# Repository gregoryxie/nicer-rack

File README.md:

# nicer-rack

hopefully nicer and not worser

View [NiceRack](http://nicerack.mit.edu:3000/)

## Installation

After downloading the repo, install all necessary depencies by running in the root folder:
`pip3 install -r requirements.txt`

## Accessing Raspberry Pi

On your own machine, SSH into the Raspi: `ssh putz@18.18.248.96`

Ask for the password if you need it. From here, you can access the Raspberry Pi's Software Configuration Tool (settings): `sudo raspi-config`

**Don't mess around with the settings.** But, if you want to update the Raspi, navigate to `8 Update` using the arrow keys, and hit enter to update. When it's done, tab your way to `Finish`, then hit enter.

You can navigate the filesystem the way any computer works. Some potentially useful commands:
* `sudo reboot`
* `sudo shutdown -h now` will safely shut down the Raspi
* `wget [url]` will download the file at the given URL to the Raspi, in whatever your working directory is.

## Web server

After making changes to config files, run `apache2ctl configtest` and make sure it doesn't throw any errors.

The main page of this site is located (on default) at `/var/www/html/index.html`. You can look at the config documentation at `/usr/share/doc/apache2/README.Debian.gz`. By default, Debian does not allow access through the web browser to any file apart of those located in `/var/www`, **public_html** directories (when enabled) and `/usr/share` (for web applications). If your site is using a web document root located elsewhere (such as in `/srv`) you may need to whitelist your document root directory in `/etc/apache2/apache2.conf`.

If you're having connection timeout issues or otherwise want to change server settings, go look at the `etc/apache2/apache2.conf` file.

To change folder location of `index.html` file:
* Change the DocumentRoot field in the config file to the correct filepath
* The default config file is at `/etc/apache2/sites-available/000-default.conf`, but you can find the nicerack config file at `etc/apache2/sites-available/nicerack.conf`
* Current location: /var/www/nicer-rack/nicer_rack_web/client/dist
* Restart apache server using `service apache2 restart`

For issues with installing llvmlite, try the following where # is the llvm version (integer?):
```
sudo apt install llvm-#
LLVM_CONFIG=llvm-config-# pip install llvmlite
```

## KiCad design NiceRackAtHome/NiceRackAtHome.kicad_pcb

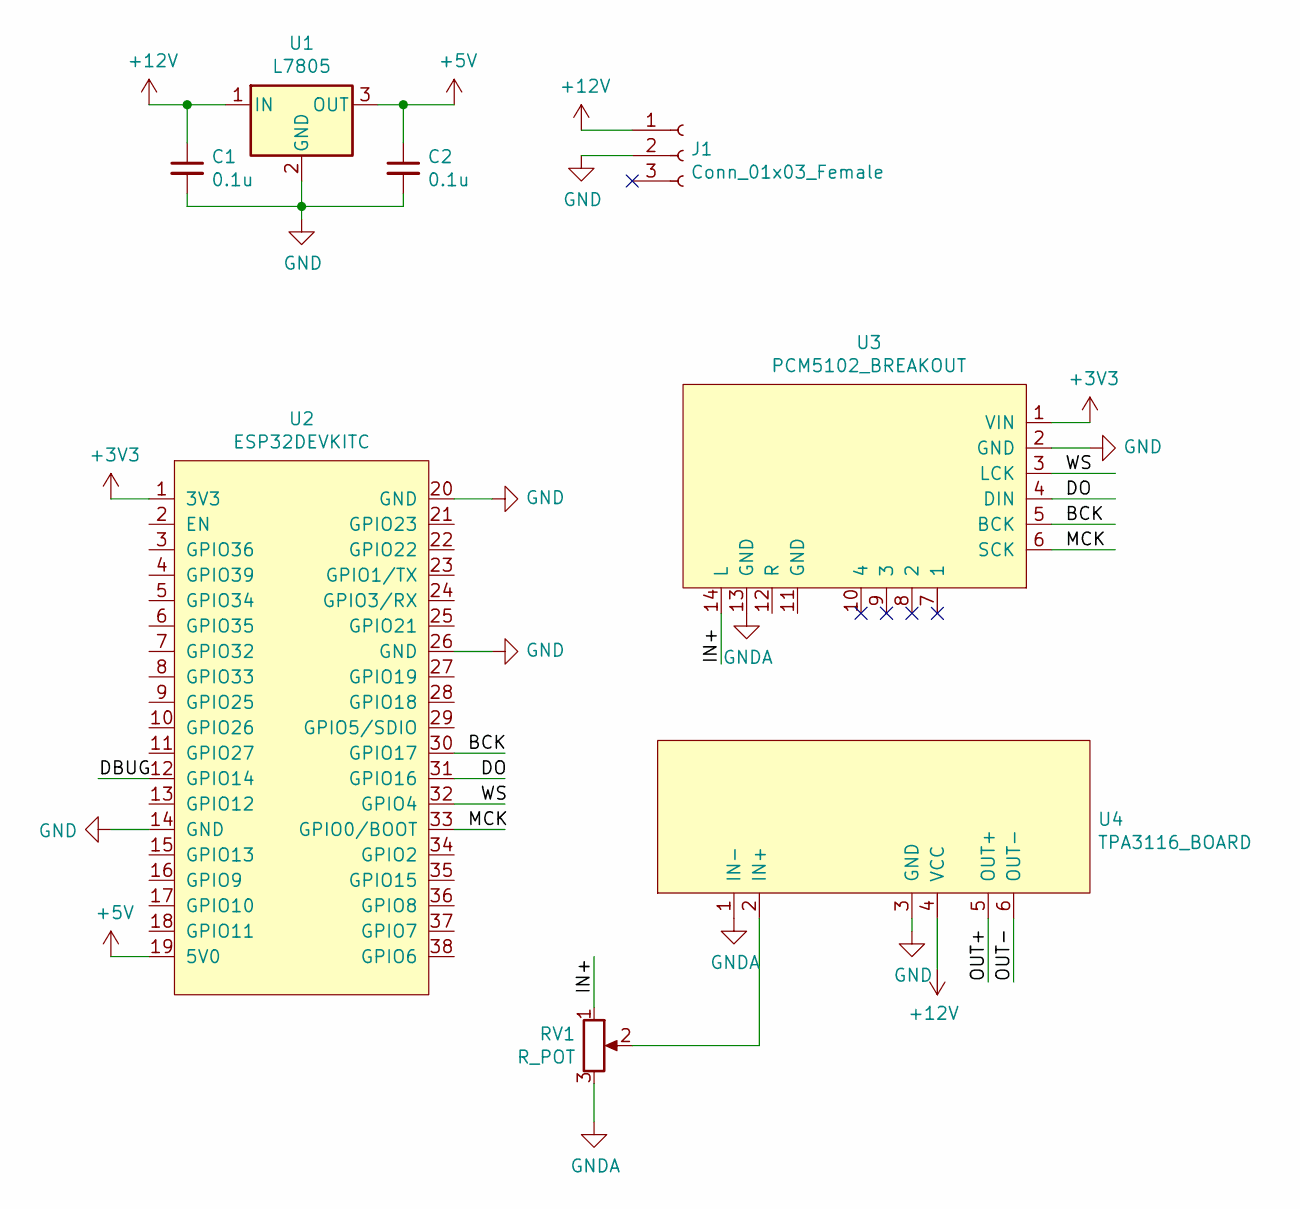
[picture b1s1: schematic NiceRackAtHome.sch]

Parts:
C1, C2: 0.1u; C_Disc_D5.1mm_W3.2mm_P5.00mm
J1: Conn_01x03_Female; 2.1mm_barrel
RV1: R_POT; Potentiometer_Alps_RK163_Single_Horizontal
U1: L7805; TO-220-3_Vertical
U2: ESP32DEVKITC; ESP32 DEVKITC
U3: PCM5102_BREAKOUT
U4: TPA3116_BOARD

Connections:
+3V3: U2.1 (3V3), U3.1 (VIN)
+5V: C2.1, U1.3 (OUT), U2.19 (5V0)
+12V: C1.1, J1.1, U1.1 (IN), U4.4 (VCC)
/BCK: U2.30 (GPIO17), U3.5 (BCK)
/DBUG: U2.12 (GPIO14)
/DO: U2.31 (GPIO16), U3.4 (DIN)
/IN+: RV1.1, U3.14 (L)
/MCK: U2.33 (GPIO0/BOOT), U3.6 (SCK)
/OUT+: U4.5 (OUT+)
/OUT-: U4.6 (OUT-)
/WS: U2.32 (GPIO4), U3.3 (LCK)
GND: C1.2, C2.2, J1.2, U1.2 (GND), U2.14 (GND), U2.20 (GND), U2.26 (GND), U3.2 (GND), U4.3 (GND)
GNDA: RV1.3, U3.13 (GND), U4.1 (IN-)
unnamed: RV1.2, U4.2 (IN+)

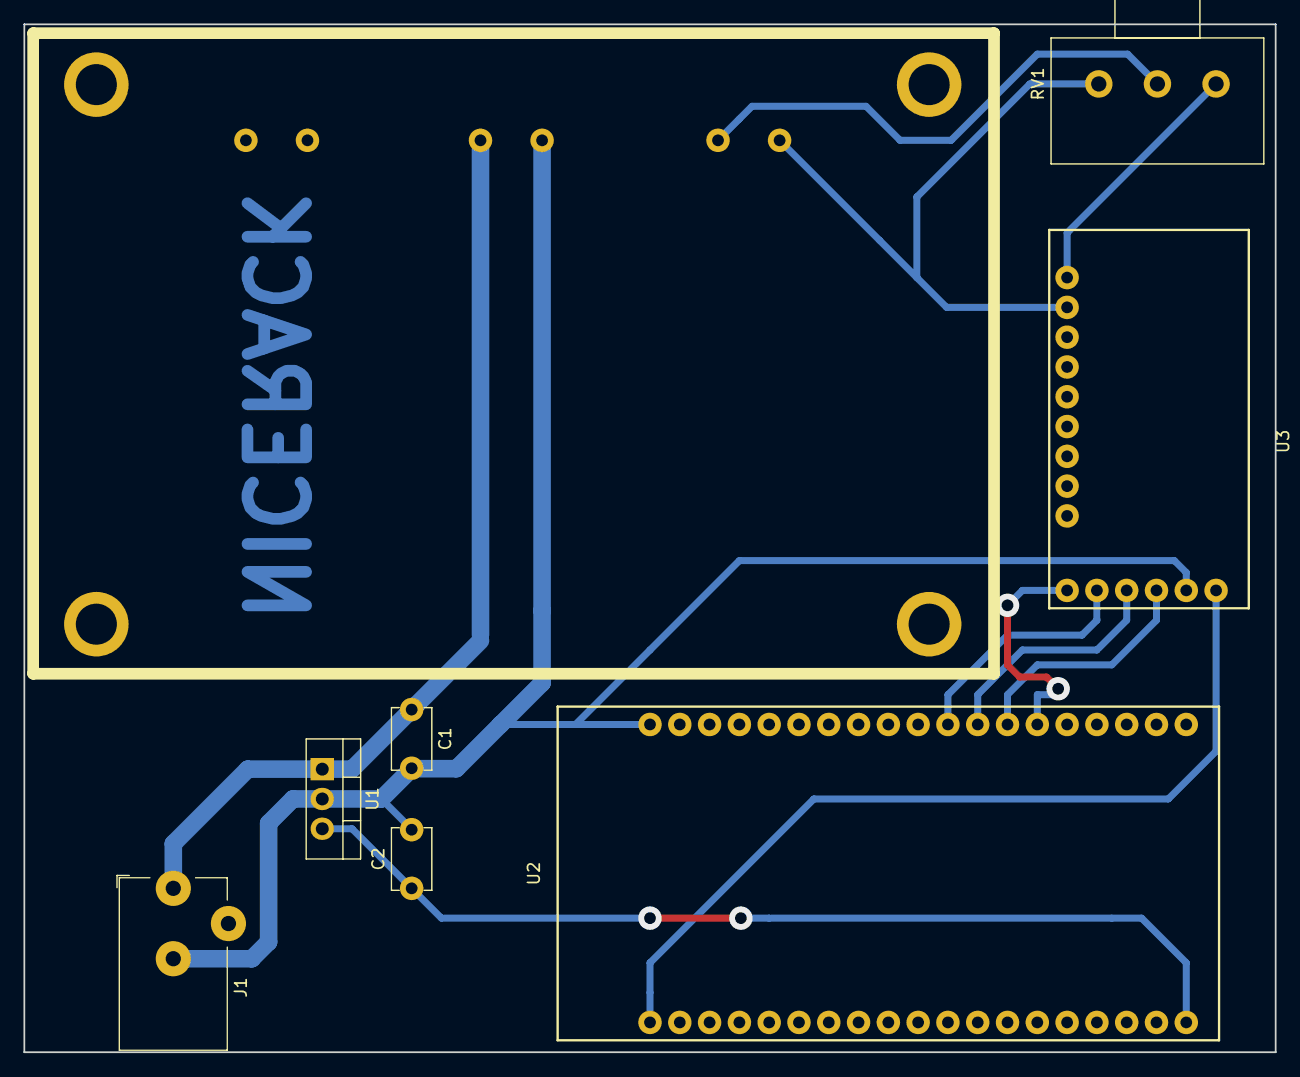
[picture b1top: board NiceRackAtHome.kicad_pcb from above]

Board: 2 copper layers, 106.7 x 87.6 mm, 8 parts (0 on the bottom side), 11 nets.

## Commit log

2022-04-11 barf data to esp
2022-04-12 batch send current song
2022-04-12 rename
2022-04-12 Initial data handling for SQL db
2022-04-12 Thumbnails in db
2022-04-12 Resolve #1
2022-04-12 Add more functions & info
2022-04-12 Implement pytube link extraction and downloading
2022-04-13 Change audio file names from titles to url query descriptors for uniqueness
2022-04-13 Update README.md
    Update to notify how to install requirements for project when running it.
2022-04-13 Change type of audio duration
2022-04-13 Do not download videos that are too long
2022-04-13 Syntax fixes & tests
2022-04-13 Set up React
2022-04-13 Implement mp3 to wav bytestream functionality
2022-04-14 Basic UI for Milestone 1
2022-04-14 Milestone 1 UI
2022-04-17 can output from constant number from i2s dac, issue with byte ordering
2022-04-17 comment
2022-04-17 Revert "can output from constant number from i2s dac, issue with byte ordering"
    This reverts commit 7e77e26b914bb95b83b7b3f90e2dd72834d1dcf4.
2022-04-17 doesnt work
2022-04-18 works, slight waveform glitching
2022-04-18 glitchy audio streaming - data being reordered in UDP packets?
2022-04-19 tcp mostly works, hangs when client disconnected
2022-04-20 Doesn't work
2022-04-20 Add link to README
2022-04-20 Non-working flask app
2022-04-20 tcp for both esp32 and server works, still slight waveform glitching
2022-04-21 Add CORS to Flask app for Webserver to Flask communication
2022-04-21 Flask works, add link submit capability
2022-04-21 Fix python imports
2022-04-21 Add Raspi info to README
2022-04-21 Queue UI
2022-04-21 Add API Routes for queue functionality
2022-04-24 changed pin defs, comm/audio done in tasks
2022-04-24 pretty good, very short blips when recv tcp data
2022-04-25 Minor fixes
2022-04-25 Queue UI, but kinda broken
2022-04-25 no sound blips on 440hz sine
2022-04-25 Fix merging bug and delete cached files in main
2022-04-27 Implement Webserver to TCP server socket, add path checking
2022-04-27 Add wav conversion to music_server
2022-04-27 Fix frame rate discontinuity
2022-04-27 Alternate frame-rate solution
2022-04-27 frame rate solution 3
2022-04-27 framerate solution attempt 4
2022-04-27 Clean code
2022-04-27 Comment out demoing bug
2022-04-27 music server locks
2022-04-27 Fix queue not showing bug
2022-04-27 Implement queueing UI functionality
2022-04-28 Add queue removal functionality
2022-05-03 Added Reactive queue, no longer need to refresh page to see updates
2022-05-03 Songs play off of queue, queue UI updates every 5 seconds
2022-05-04 Add package to requirements
2022-05-04 Link queue to TCP server. Still some queue management bugs
2022-05-04 Implement locks for queue operations
2022-05-04 Fix small bug in music_server
2022-05-04 queue half work
2022-05-04 Change locking
2022-05-04 i2s pin changes for pcb
2022-05-05 Add play/pause functionality
2022-05-05 Fix song sample bug
2022-05-05 Search function & UI
2022-05-05 Download stuff
2022-05-05 Fix needing to reload to see updated display
2022-05-09 Add threaded queue for commands in music_server, fix queue indexing bug when last song runs out
2022-05-09 Initial server README
2022-05-09 Change references to localhost
2022-05-09 Add server setup info to README
2022-05-09 Add node module files
    Not sure why these register as changed files so I'm adding them in waves just in case
2022-05-09 Add client src component modules
2022-05-09 Revert nicerack -> localhost references
2022-05-09 Revert other localhost references
2022-05-10 Apply stash for link handler system path
2022-05-10 stuff
2022-05-10 It works I think
2022-05-10 Change host ip in package.json
2022-05-10 added comments
2022-05-11 kill client thread on timeouts
2022-05-11 change ip
2022-05-11 adding pcb files
